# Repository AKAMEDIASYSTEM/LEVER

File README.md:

# LEVER
####Experiments in electrovibration interaction strategies, inspired by Disney Research papers "Tesla Touch" and "Revel"

Here are the papers I am trying to implement here:
http://www.ivanpoupyrev.com/e-library/2010/teslatouchUIST2010.pdf

http://www.disneyresearch.com/wp-content/uploads/REVEL.pdf

###Summary
Basically, the papers describe a way to augment surfaces with _dynamically changeable tactile properties_ - a surface can change from sticky to slippery basically at will.

###Status
This work is incomplete and ongoing - for one thing, while the circuit decribed here works, I have yet to implement current-sensing feedback as described in the papers. I'm eager to accomplish this because it allows normalization of sensation across people, skin moistures, and time.

###Why I am interested
I'm interested in experimenting with this technology as applied to various notification strategies, particularly on mobile and wearable devices.
I would like to develop interactions in which a person queries a "stack" of stuff waiting for them, rather than being interrupted by a push notification.
The appeal of this technology in this application is that it's totally silent and able to be done without interrupting the person's conversation by stealing focus.
If this technology is implemented on the back of a mobile device, for example, simply rubbing a finger along the back of the phone is all that is needed to see the magnitude of my "stack."
Of course, "stack" can be many things: number of unread emails, number of to-do items, number of places of interest very near me, and so on.

###This repository
The purpose of this repo is to make my work shareable - I had a fair amount of trouble trying to go from the research paper to a safe, working circuit, and I'm hoping to save others some work.

The circuitboard isn't what I would put onto a phone - it is instead a platform for trying out different waveforms, intensities, and so on.

The intent is that you will use the board to figure out the correct implementation details and then generate your own board with a more appropriate layout.

###Requirements
You should follow the BOM pretty precisely unless you know what you are doing. The circuit is designed to work with a 9v battery and I will be trying to allow smaller/more power supplies to work with it. The microcontroller is a Teensy 3.1

###Thanks
I'm so grateful to Disney Research, Ivan Poupyrev, Olivier Bau, and others who worked on the papers for making their work available - I never would have known aobut this cool phoneomenon without their shared work! Thanks as well to nytlabs for supporting my explorations and letting me share in kind.

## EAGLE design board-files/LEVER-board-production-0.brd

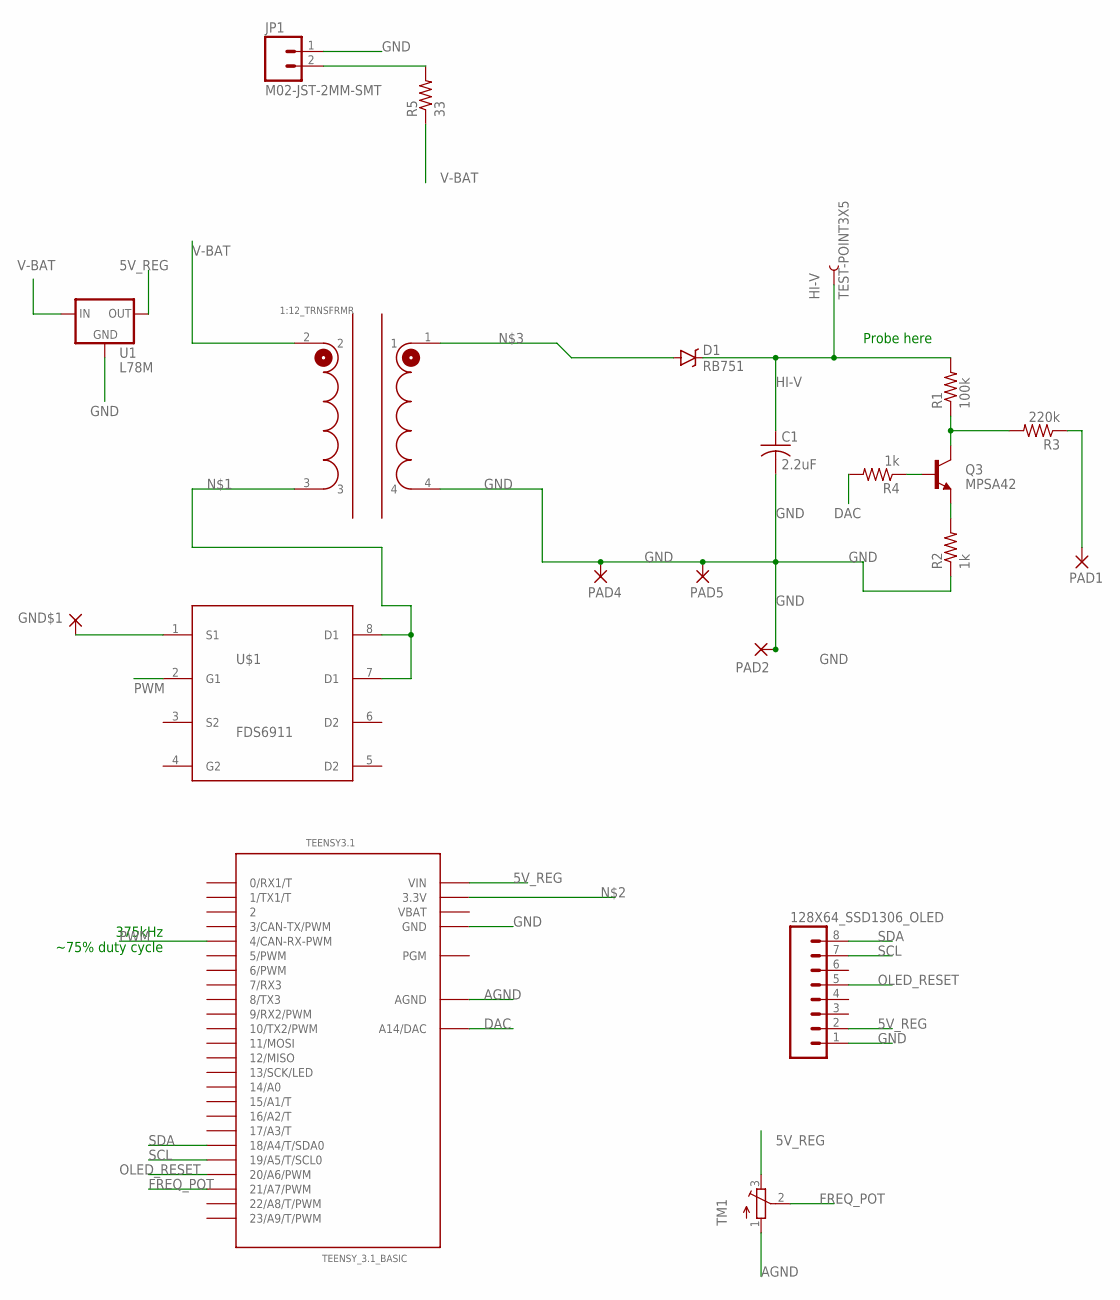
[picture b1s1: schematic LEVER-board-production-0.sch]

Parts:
1:12_TRNSFRMR: PA0367
128X64_SSD1306_OLED: M08LOCK; 1X08_LOCK
C1: 2.2uF; C1812
D1: RB751; TO263
GND$1: WIREPADSMD5-2,5; 5-2,5
HI-V: TEST-POINT3X5; PAD.03X.05
JP1: M02-JST-2MM-SMT; JST-2-SMD
PAD1, PAD2, PAD4, PAD5: WIREPADSMD5-2,5; 5-2,5
Q3: MPSA42; TO-92
R1: 100k; R2010
R2, R4: 1k; 1206
R3: 220k; R2010
R5: 33; 1206
TEENSY3.1: TEENSY_3.1_BASIC
TM1: TRIMPOT3386; TRIM-3386
U1: L78M; DPAK
U$1: FDS6911; SO8

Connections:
5V_REG: 128X64_SSD1306_OLED.2, TEENSY3.1.VIN, TM1.3 (E), U1.3 (OUT)
AGND: TEENSY3.1.AGND, TM1.1 (A)
DAC: R4.2, TEENSY3.1.A14 (A14/DAC)
FREQ_POT: TEENSY3.1.21/A7 (21/A7/PWM), TM1.2 (S)
GND: 1:12_TRNSFRMR.4, 128X64_SSD1306_OLED.1, C1.2, GND$1.1, JP1.1 (2), PAD2.1, PAD4.1, PAD5.1, R2.1, TEENSY3.1.GND, TEENSY3.1.GND1 (GND), U1.4 (GND), U$1.1 (S1)
HI-V: C1.1, D1.1 (C), HI-V.P$1, R1.2
unnamed: 1:12_TRNSFRMR.3, U$1.7 (D1), U$1.8 (D1)
unnamed: TEENSY3.1.3.3V, TEENSY3.1.3.3V1 (3.3V)
unnamed: 1:12_TRNSFRMR.1, D1.2 (A)
unnamed: JP1.2 (1), R5.2
unnamed: Q3.1 (C), R1.1, R3.2
unnamed: Q3.3 (E), R2.2
unnamed: Q3.2 (B), R4.1
OLED_RESET: 128X64_SSD1306_OLED.5, TEENSY3.1.20/A6 (20/A6/PWM)
PAD: PAD1.1, R3.1
PWM: TEENSY3.1.4 (4/CAN-RX-PWM), U$1.2 (G1)
SCL: 128X64_SSD1306_OLED.7, TEENSY3.1.19/A5 (19/A5/T/SCL0)
SDA: 128X64_SSD1306_OLED.8, TEENSY3.1.18/A4 (18/A4/T/SDA0)
V-BAT: 1:12_TRNSFRMR.2, R5.1, U1.1 (IN)
VBAT: TEENSY3.1.VBAT

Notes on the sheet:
Probe here
375kHz ~75% duty cycle

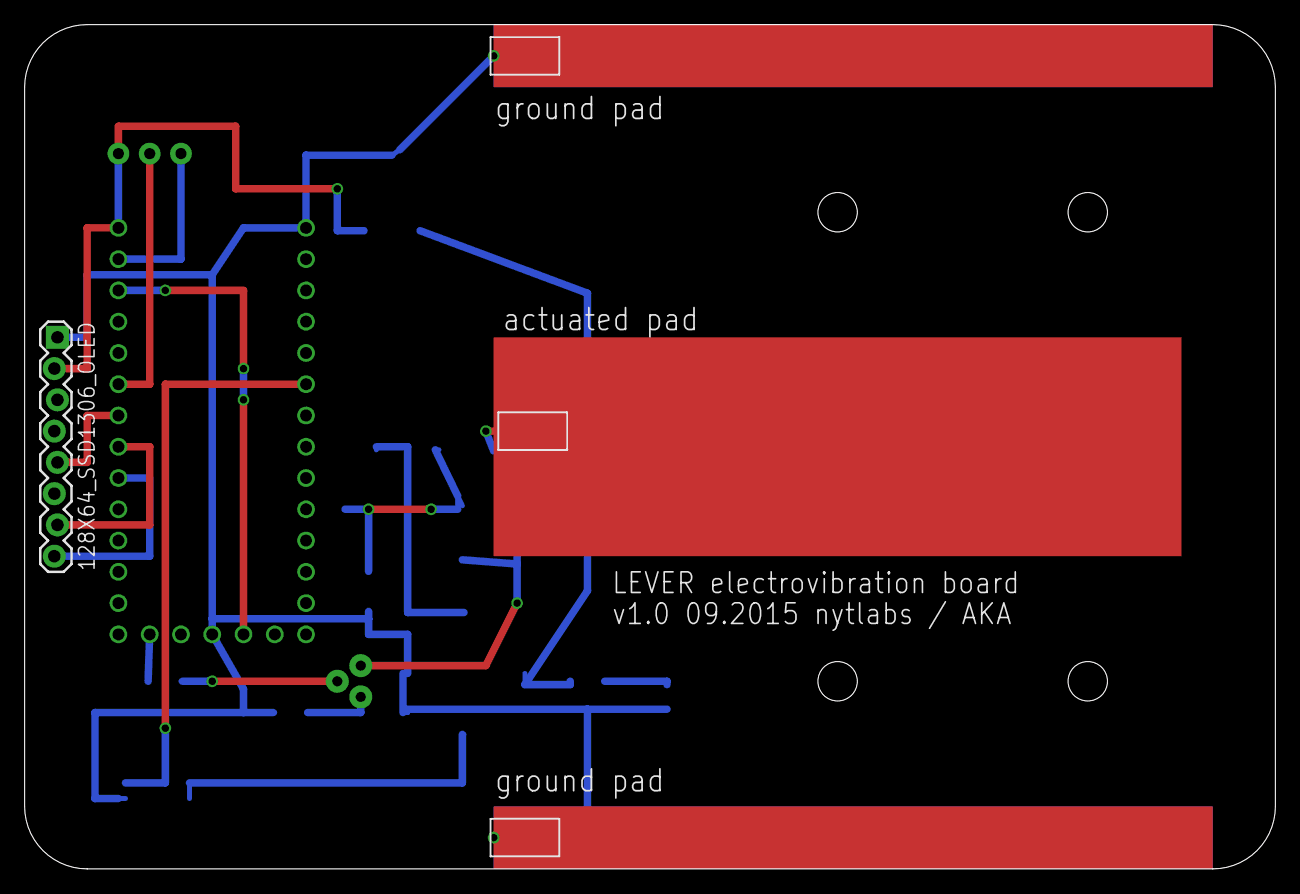
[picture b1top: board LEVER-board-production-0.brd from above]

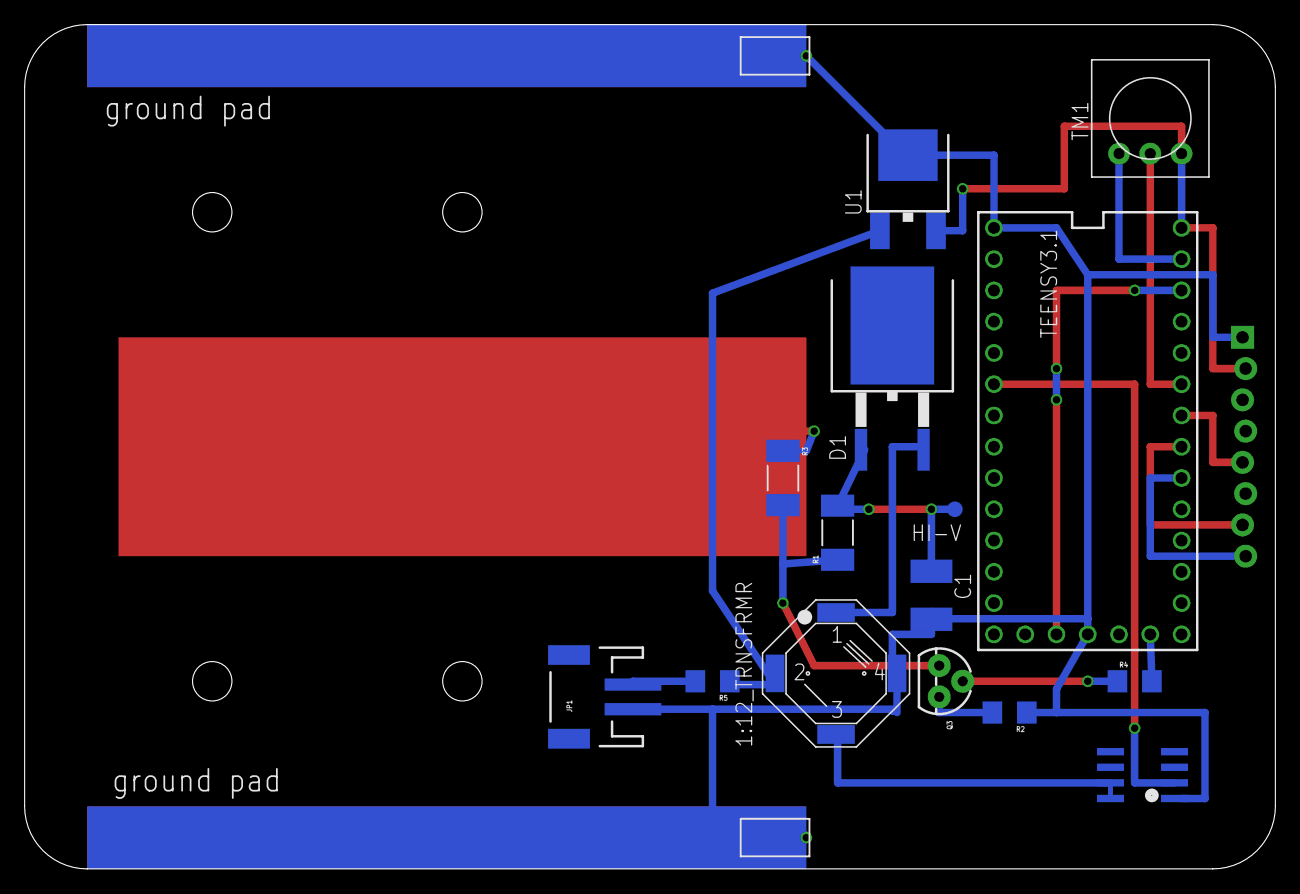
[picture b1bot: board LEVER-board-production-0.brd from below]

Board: 2 copper layers, 101.6 x 68.6 mm, 21 parts (17 on the bottom side), 19 nets.

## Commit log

2015-09-08 adding extant firmware and board files
2015-09-08 added display code which failed to add before for some reason
2015-09-08 update gitignore
2015-09-08 added current BOM
2015-09-09 stubbing out new duty cycle and waveform functionality
2015-09-09 updating dutyPot code
2015-09-10 added manual pwm modulation - discovered pwn can go all the way down to 30% and still generate ~160v, excellent. Affords new, rubbery feeling at low-end of freq and pwm scales
2015-09-11 adding amplPot
2015-09-11 adding amplPot but not tested
2015-09-14 added variable waveforms, tested fine, still need to make triangle-wave code
2015-09-14 fixed offset and amplitude scaling problems - sensor board is a little shaky, which affects screen update rate, which affects circuit. will have to stabilize those sigs (more decoupling, probably) an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
2015-09-14 debug display format updates, untested
2015-09-23 added aux firmware for testing v1 of OSH board
2015-09-24 swapping triangle waveform for NOISE, still needs to be tested a bit
2015-09-24 stabilizing display upon startup, added measured real-freq ranges to boardtesting firmware
2015-09-25 added some futre planning notes
2015-09-29 updating display code, duty cycle, in prep for first feedback tests
2015-09-29 amplitude now works properly, after inversion right before writing to the DAC. However, adding updateDisplay() logic to all the other pots failed, slowing the whole loop down to an unusable extent. T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
2015-09-29 saving some space by commenting out unused wavetable
2015-10-05 updating firmware to accept button-and-encoder, should make screen more stable and UI easier
2015-10-07 moving encoder firmware over to main sketch
2015-10-08 still trying to make encoder work with WAVE selection, everything else working well
2015-10-08 got encoder working acceptably and initial conditions set better
2015-10-09 updated bom
2015-10-14 boardtesting firmware inconsequential change

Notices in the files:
parts and their libraries:
SparkFun-DiscreteSemi: Licensing: Creative Commons ShareAlike 4.0 International - https://creativecommons.org/licenses/by-sa/4.0
